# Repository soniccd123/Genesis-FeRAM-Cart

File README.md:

# Genesis FeRAM Cart
A open Sega Genesis cartridge PCB with save feature

This projects uses a 27C322 4MB EPROM Chip and a FM1808 32KB FeRAM as save storage. It was developed in KiCAD and tested in real hardware.

In the actual state, this cartridge features:

- Suports Genesis and 32X software
- ROM Support for up to 4MB
- Save support for all ROM sizes (Selection for <2MB/4MB by jumper)
- 32KB of FeRAM for saving
- No need for battery for saving
- Rudimentary ROM bank switch (Permits multiple games on same ROM)

This project is possible thanks to TmEE (NESdev Forums, SRAM wiring schematics) and Rene Richard (db-electronics on GitHUB, KiCAD libs for the Genesis cart connector).

# Component List:
- U1 74HC74;
- U2 FM1808B;
- U3 74HC139 (or LS);
- U4 27C322 (May use other 27CXX memories with some minor modifications);
- R1, R2, R3, R4 1K Resistors;
- SW1 4 channel DIP Switch;
- C1, C2, C3 10nF Capacitors;

# How to use:
Bank Switching: The user may write multiple roms to the same EPROM, the DIP switch controls which area of the EPROM is read by the Genesis/Mega Drive; The minimum bank size is 256KB. Each of the switches connect a memory address line between the system and the EPROM: when the switch is on, the respective address line is controlled by the Sega Genesis; When off, the EPROM adress line is pulled-up and cut from Genesis control. the address lines are A20, A19, A18, A17 (considering LSB as A0). To select the desired bank, turn the switches on and off acordingly to the begining address that the ROM occupies in the EPROM.

Examples:

ROM_x begin at 0x100000 -> Switch just A19 off (pull-up);           
ROM_y begin at 0x180000 -> Switch A19 and A18 off;

This technique may not be compatible with save supporting Genesis software.

How to make multirom file: Just use the CMD command "copy /b rom_x.bin + rom_y.bin + rom_z.bin rom_result.bin" to join them to one file. One may join how many ROMs he wants to, just be shure that the result file is smaller than the total size of the EPROM and that the ROMs fit correctly to each desired bank to make software switching possible.

JP1 jumper: This jumper is the result of some tests with varied sized Save RAM suporting software. This jumper is necessary for software bigger or smaller than 2MB to correctly save and detect the FeRAM. For software bigger than 2M, one must connect (with solder blob, 0K resistor, etc) the >2MB part of the jumper; for smaller or equal to 2MB software, one must do the same with the <2MB part of the jumper.

Other than that, just write to your EPROM and happy playing!

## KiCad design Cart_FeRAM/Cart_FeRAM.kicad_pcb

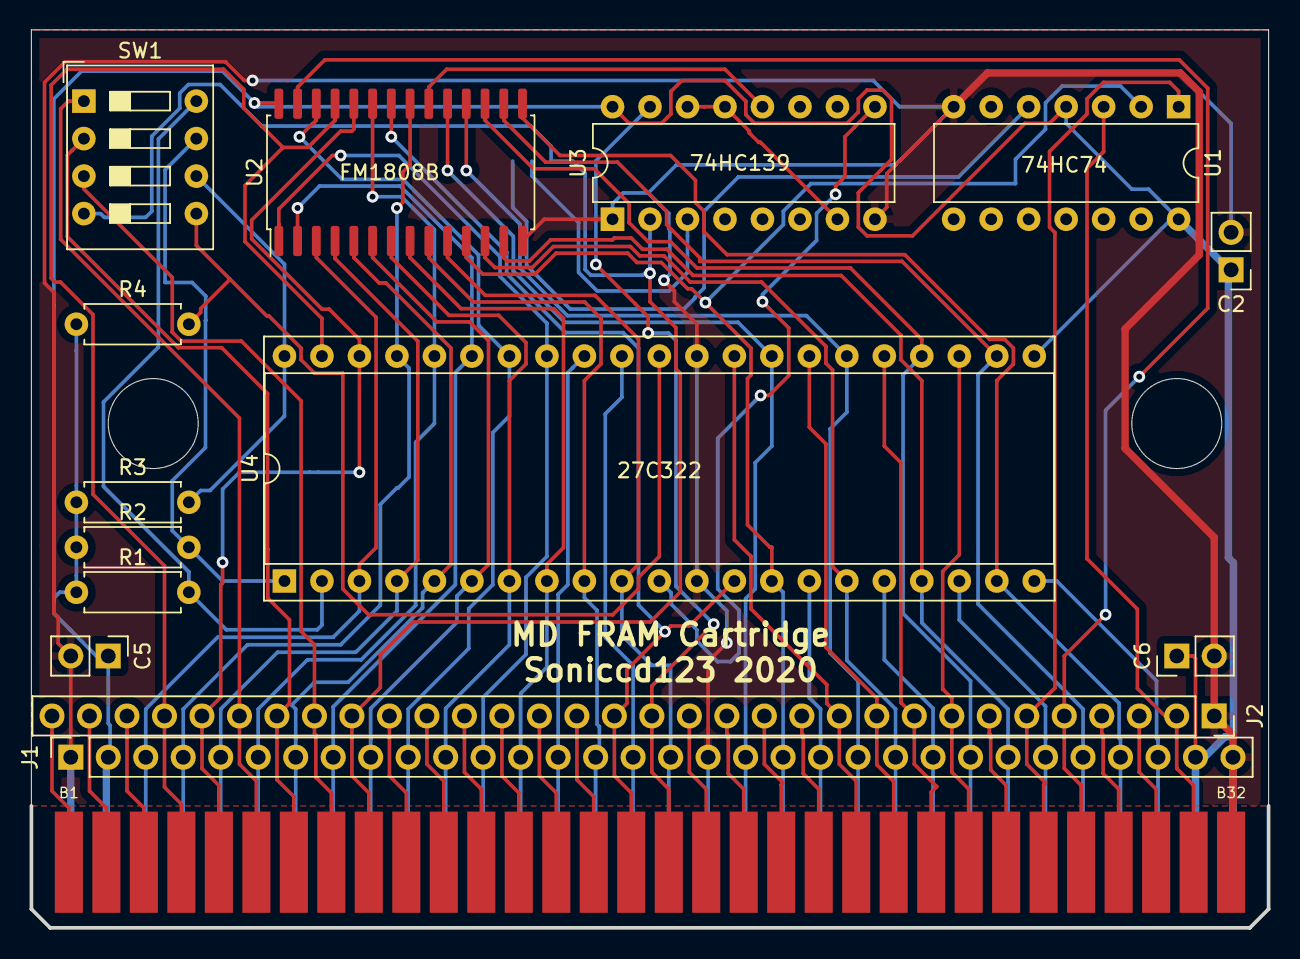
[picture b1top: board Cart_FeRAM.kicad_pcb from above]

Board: 2 copper layers, 83.8 x 60.7 mm, 16 parts (1 on the bottom side), 69 nets.

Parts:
C2, C5, C6: C; PinHeader_1x02_P2.54mm_Vertical
CON1: GENESIS-EDGE
J1, J2: Conn_01x32_Male; PinSocket_1x32_P2.54mm_Vertical
JP1: <2M/4M; SolderJumper-3_P1.3mm_Open_Pad1.0x1.5mm
R1, R2, R3, R4: 1K; R_Axial_DIN0207_L6.3mm_D2.5mm_P7.62mm_Horizontal
SW1: SW_DIP_x04; SW_DIP_SPSTx04_Slide_9.78x12.34mm_W7.62mm_P2.54mm
U1: 74HC74; DIP-14_W7.62mm
U2: FM1808B-SG; SOIC-28W_7.5x17.9mm_P1.27mm
U3: 74LS139; DIP-16_W7.62mm
U4: 27C322; DIP-42_W15.24mm_Socket

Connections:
+5V: C2.1, C5.1, C6.1, CON1.A2, CON1.A31, J1.2, J1.31, R1.1, R2.1, R3.1, R4.1, U1.4, U1.14, U2.28, U3.16, U4.22
/A0: CON1.A17, J1.17, U2.10, U4.10
/A1: CON1.A15, J1.15, U2.9, U4.9
/A2: CON1.A13, J1.13, U2.8, U4.8
/A3: CON1.A11, J1.11, U2.7, U4.7
/A4: CON1.A9, J1.9, U2.6, U4.6
/A5: CON1.A7, J1.7, U2.5, U4.5
/A6: CON1.A5, J1.5, U2.4, U4.4
/A7: CON1.A3, J1.3, U2.3, U4.3
/A8: CON1.B4, J2.29, U2.25, U4.41
/A9: CON1.B5, J2.28, U2.24, U4.40
/A10: CON1.A4, J1.4, U2.21, U4.39
/A11: CON1.A6, J1.6, U2.23, U4.38
/A12: CON1.A8, J1.8, U2.2, U4.37
/A13: CON1.A10, J1.10, U2.26, U4.36
/A14: CON1.A12, J1.12, U2.1, U4.35
/A15: CON1.A14, J1.14, U4.34
/A16: CON1.A16, J1.16, U4.33
/A17: R1.2, SW1.8, U4.2
/A18: R2.2, SW1.7, U4.1
/A19: R3.2, SW1.6, U4.42
/A20: R4.2, SW1.5, U4.32
/CART_A17: CON1.B6, J2.27, SW1.1
/CART_A18: CON1.B7, J2.26, SW1.2
/CART_A19: CON1.B8, J2.25, SW1.3
/CART_A20: CON1.B9, J2.24, JP1.1, SW1.4, U3.2
/CE: CON1.B17, J2.16, U3.15
/D0: CON1.A20, J1.20, U1.2, U2.11, U4.14
/D1: CON1.A23, J1.23, U2.12, U4.16
/D2: CON1.A26, J1.26, U2.13, U4.18
/D3: CON1.A29, J1.29, U2.15, U4.20
/D4: CON1.A28, J1.28, U2.16, U4.23
/D5: CON1.A25, J1.25, U2.17, U4.25
/D6: CON1.A22, J1.22, U2.18, U4.27
/D7: CON1.A19, J1.19, U2.19, U4.29
/D8: CON1.A21, J1.21, U4.15
/D9: CON1.A24, J1.24, U4.17
/D10: CON1.A27, J1.27, U4.19
/D11: CON1.A30, J1.30, U4.21
/D12: CON1.B25, J2.8, U4.24
/D13: CON1.B24, J2.9, U4.26
/D14: CON1.B23, J2.10, U4.28
/D15: CON1.B22, J2.11, U4.30
/OE: CON1.B16, J2.17, U2.22, U4.13
/RESET: CON1.B27, J2.6, U1.1
/ROM_CE: U3.9, U4.11
/SRAM_CE: U2.20, U3.12
/TIME: CON1.B31, J2.2, U1.3
/WE: CON1.B28, J2.5, U2.27
GND: C2.2, C5.2, C6.2, CON1.A1, CON1.A18, CON1.A32, CON1.B32, J1.1, J1.18, J1.32, J2.1, U1.7, U2.14, U3.1, U3.8, U4.12, U4.31
unnamed: CON1.B1, J2.32
unnamed: CON1.B2, J2.31
unnamed: CON1.B3, J2.30
unnamed: CON1.B10, J2.23
unnamed: CON1.B11, J2.22
unnamed: CON1.B12, J2.21
unnamed: CON1.B13, J2.20
unnamed: CON1.B14, J2.19
unnamed: CON1.B15, J2.18
unnamed: CON1.B18, J2.15
unnamed: CON1.B19, J2.14
unnamed: CON1.B20, J2.13
unnamed: CON1.B21, J2.12
unnamed: CON1.B26, J2.7
unnamed: CON1.B29, J2.4
unnamed: CON1.B30, J2.3
unnamed: JP1.2, U3.3
unnamed: JP1.3, U1.5
unnamed: U3.7, U3.13, U3.14

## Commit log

2020-08-02 Updated board design, some project clean up
2020-08-02 Update README.md
    Adicional information
2020-08-02 Updated PCB production files acording to latest design changes
2020-09-17 Added IC values to silkscreen, added JP1 identification to silkscreen, added BOM
2020-09-17 Update README.md
    Added important info
